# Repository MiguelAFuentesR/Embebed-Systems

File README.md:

# Embebed-Systems

This repository contains the proposed developments for the projects belonging to the subject embedded systems.

The repository contains all the documentation related to the development of applications in the IoT field, communication protocols and applications in the ESP32 microcontroller. 

Repository Elaborated by: https://www.linkedin.com/in/miguelafuentesr/

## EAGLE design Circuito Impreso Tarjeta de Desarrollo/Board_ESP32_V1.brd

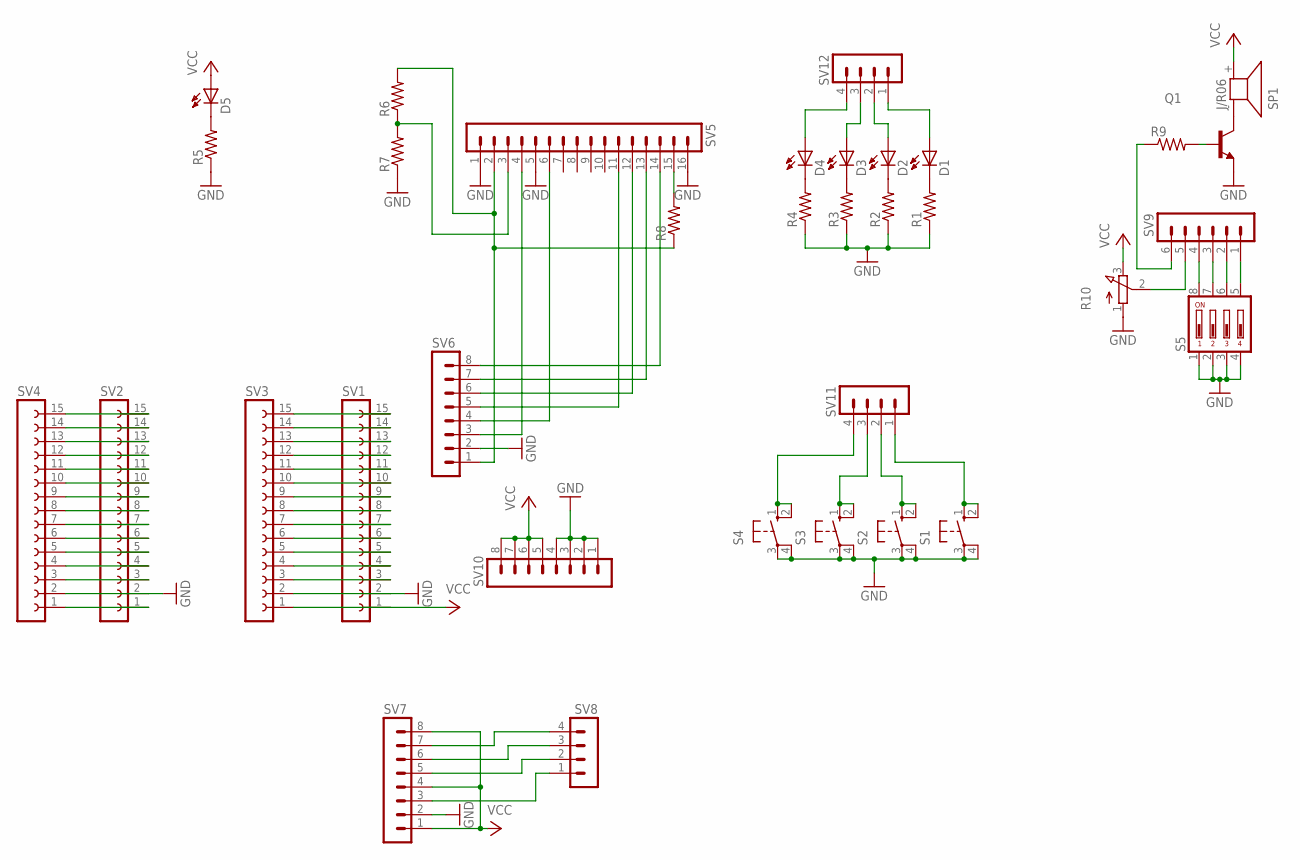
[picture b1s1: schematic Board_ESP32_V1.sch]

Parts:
D1, D2, D3, D4, D5: LED3MM
Q1: 2N3904; TO92
R1, R2, R3, R4, R5, R6, R7, R8, R9: R-US_0207/10; 0207/10
R10: 3RP/1610N
S1, S2, S3, S4: 10-XX; B3F-10XX
S5: DIP04YL
SP1: J/R06
SV1, SV2, SV3, SV4: FE15-1; FE15
SV5: MA16-1
SV6, SV7, SV10: MA08-1
SV8, SV11, SV12: MA04-1
SV9: MA06-1

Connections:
GND: Q1.3 (E), R1.1, R2.1, R3.1, R4.1, R5.1, R7.1, R10.1 (A), S1.3, S1.4 (P1), S2.3, S2.4 (P1), S3.3, S3.4 (P1), S4.3, S4.4 (P1), S5.1, S5.2, S5.3, S5.4, SV1.2, SV2.2, SV3.2, SV4.2, SV5.1, SV5.5, SV5.16, SV6.2, SV7.2, SV10.1, SV10.2, SV10.3, SV10.4
unnamed: SV5.14, SV6.8
unnamed: SV5.6, SV6.4
unnamed: SV5.11, SV6.5
unnamed: SV5.12, SV6.6
unnamed: SV5.13, SV6.7
unnamed: SV5.4, SV6.3
unnamed: R6.2, R8.1, SV5.2, SV6.1
unnamed: D1.A, SV12.1
unnamed: D2.A, SV12.2
unnamed: D3.A, SV12.3
unnamed: D4.A, SV12.4
unnamed: SV7.3, SV8.1
unnamed: SV7.5, SV8.2
unnamed: SV7.6, SV8.3
unnamed: SV7.7, SV8.4
unnamed: D1.K (C), R1.2
unnamed: D2.K (C), R2.2
unnamed: D3.K (C), R3.2
unnamed: D4.K (C), R4.2
unnamed: S5.5, SV9.1
unnamed: S5.6, SV9.2
unnamed: S5.7, SV9.3
unnamed: S5.8, SV9.4
unnamed: S4.1 (S), S4.2 (S1), SV11.4
unnamed: S3.1 (S), S3.2 (S1), SV11.3
unnamed: S2.1 (S), S2.2 (S1), SV11.2
unnamed: S1.1 (S), S1.2 (S1), SV11.1
unnamed: R10.2 (S), SV9.5
unnamed: D5.K (C), R5.2
unnamed: R8.2, SV5.15
unnamed: R6.1, R7.2, SV5.3
unnamed: Q1.1 (C), SP1.- (1)
unnamed: Q1.2 (B), R9.2
unnamed: R9.1, SV9.6
unnamed: SV2.3, SV4.3
unnamed: SV2.4, SV4.4
unnamed: SV2.5, SV4.5
unnamed: SV2.6, SV4.6
unnamed: SV2.7, SV4.7
unnamed: SV2.8, SV4.8
unnamed: SV2.9, SV4.9
unnamed: SV2.10, SV4.10
unnamed: SV2.11, SV4.11
unnamed: SV2.12, SV4.12
unnamed: SV2.13, SV4.13
unnamed: SV2.14, SV4.14
unnamed: SV2.15, SV4.15
unnamed: SV2.1, SV4.1
unnamed: SV1.15, SV3.15
unnamed: SV1.14, SV3.14
unnamed: SV1.13, SV3.13
unnamed: SV1.12, SV3.12
unnamed: SV1.11, SV3.11
unnamed: SV1.10, SV3.10
unnamed: SV1.7, SV3.7
unnamed: SV1.8, SV3.8
unnamed: SV1.9, SV3.9
unnamed: SV1.6, SV3.6
unnamed: SV1.5, SV3.5
unnamed: SV1.4, SV3.4
unnamed: SV1.3, SV3.3
VCC: D5.A, R10.3 (E), SP1.+ (2), SV1.1, SV3.1, SV7.1, SV7.4, SV7.8, SV10.5, SV10.6, SV10.7, SV10.8

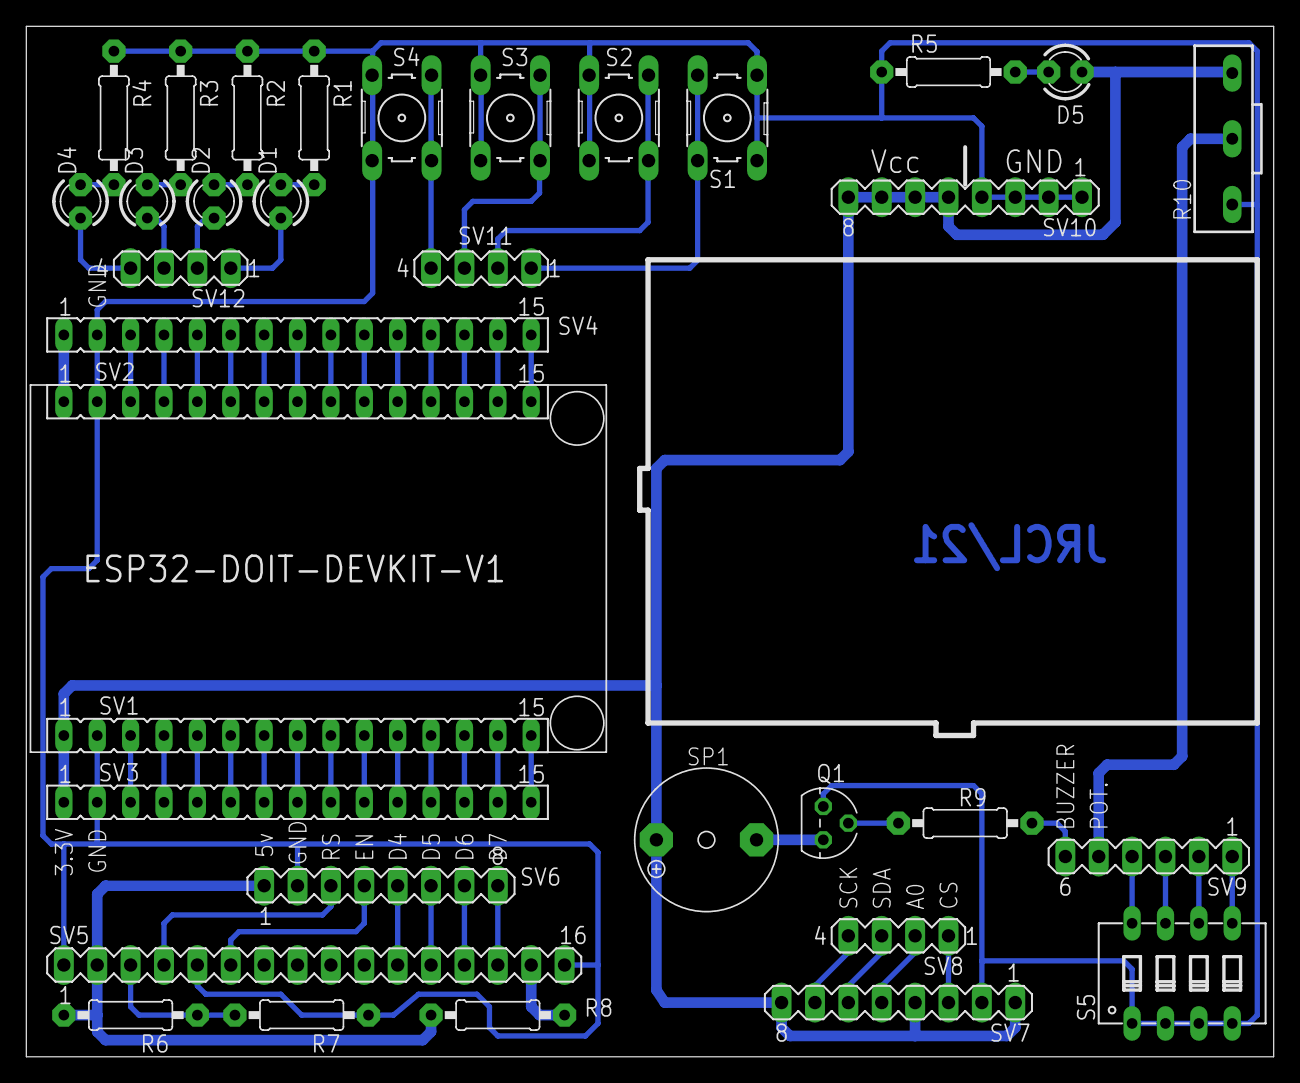
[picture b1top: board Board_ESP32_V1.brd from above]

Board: 2 copper layers, 94.9 x 78.4 mm, 34 parts (0 on the bottom side), 63 nets.
